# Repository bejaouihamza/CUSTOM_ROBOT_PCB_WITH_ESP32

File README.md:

# CUSTOM_ROBOT_PCB_WITH_ESP32
A custom-designed PCB for robotics applications, featuring the ESP32-C3-WROOM-2 microcontroller with WiFi & Bluetooth connectivity, motor control via the L298P H-bridge, efficient power management, and USB isolation for safe programming.

Key Features
🚀 Core Components
ESP32-C3-WROOM-2 – RISC-V-based MCU with WiFi 4 & Bluetooth 5 (BLE)

L298P Motor Driver – Dual H-bridge for controlling two DC motors or one stepper motor

CH340C USB-UART – Reliable serial communication for programming and debugging

USB Battery Isolation – Prevents backpowering issues during programming

12V Battery Input – Supports LiPo/Li-ion batteries with proper protection

⚡ Power Management
Buck Converter (12V → 5V/3.3V) – Efficient voltage regulation for MCU & peripherals

Battery Monitoring – Optional voltage divider for battery level sensing

🔌 Connectivity & I/O
USB-C Port – For programming & serial communication

Bluetooth/WiFi Control – Remote operation via smartphone or PC

GPIO Breakout – Access to unused ESP32 pins for sensors & expansions

🛠️ Applications
Autonomous Robots (Line-following, obstacle avoidance)

RC Vehicles (WiFi/Bluetooth-controlled)

IoT-Enabled Robotics (Telemetry, remote control)

📌 Schematic & Design Files
Designed in KiCad (schematics & PCB layout included)

Gerber files ready for manufacturing

🔧 Getting Started
Flash the ESP32-C3 via USB-C .

Power via 12V battery – The buck converter supplies stable 5V/3.3V to the system.

Control motors via the L298P using PWM signals from the ESP32.

Use WiFi/BLE for wireless communication (Arduino/ESP-IDF supported).

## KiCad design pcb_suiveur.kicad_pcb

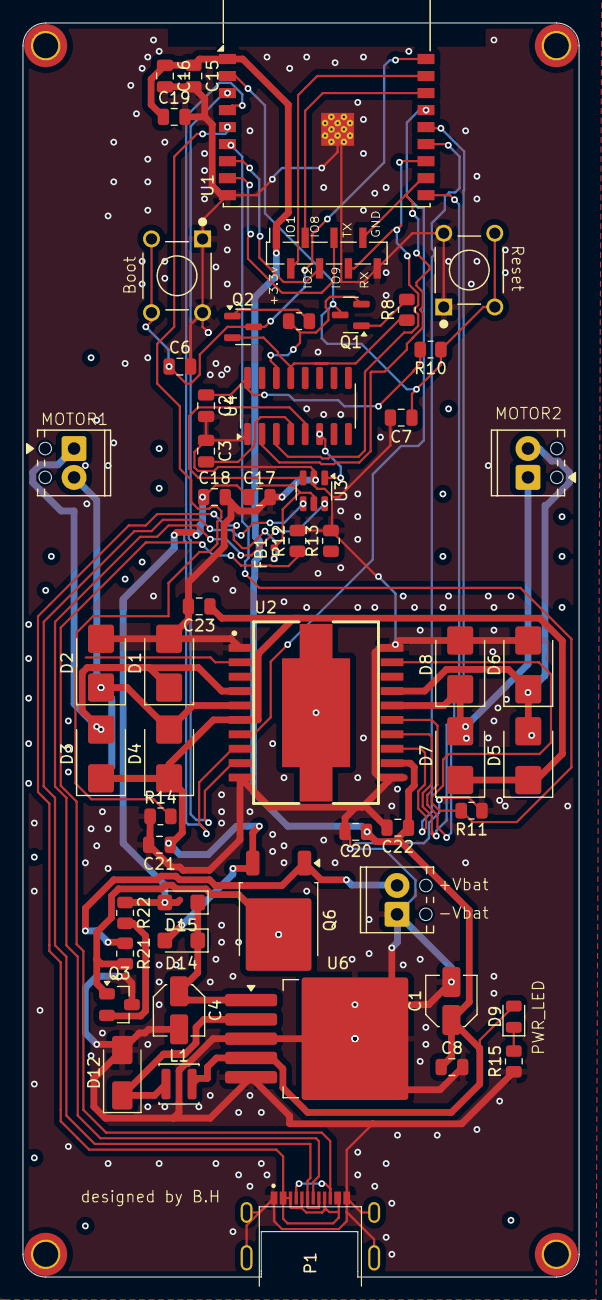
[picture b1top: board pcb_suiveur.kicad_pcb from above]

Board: 2 copper layers, 49.0 x 110.5 mm, 60 parts (0 on the bottom side), 42 nets.

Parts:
C1: 330uf; C_Elec_4x5.4
C2, C3, C6, C8, C15, C20, C21, C22, C23: 0.1u; C_0805_2012Metric
C4: 470u; C_Elec_4x5.4
C7, C17: 1u; C_0805_2012Metric
C16: 22u; C_0805_2012Metric
C18, C19: 10u; C_0805_2012Metric
D1, D2, D3, D4, D5, D6, D7, D8: 1N5819; D_SMB
D9: LED; LED_0805_2012Metric
D12: SS34; D_SMA
D14, D15: 1N5819; D_SMF
FB1: FerriteBead; L_0402_1005Metric
H1, H2, H3, H4: MountingHole; MountingHole_2.2mm_M2_DIN965_Pad_TopOnly
J1: Conn_01x08_Socket; PinSocket_1x08_P1.27mm_Vertical_SMD_Pin1Right
J2, J3, J4_battery3: Screw_Terminal_01x02; TerminalBlock_Phoenix_MPT-0,5-2-2.54_1x02_P2.54mm_Horizontal
L1: 33u; L_APV_ANR3010
P1: USB_C_Plug_USB2.0; TE_2340901-1
Q1, Q2: BC817; SOT-23
Q3: NPN; SuperSOT-3
Q6: NMOS; TO-252-2
R8, R9, R10, R15: 10K; R_0805_2012Metric
R11, R14: 1; R_0805_2012Metric
R12, R13: 5.1K; R_0805_2012Metric
R21: 10k; R_0805_2012Metric
R22: 4.7k; R_0805_2012Metric
SW1, SW2: 1101NE; SW_FSM8JH
U1: ESP32-C3-WROOM-02
U2: L298P; SOIC127P1420X360-20N
U3: USBLC6-2SC6; SOT-23-6
U4: CH340C; SOIC-16_3.9x9.9mm_P1.27mm
U6: LM2596S-3.3; TO-263-5_TabPin3

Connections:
3.3V: C2.1, R10.2, U4.16 (VCC)
+3.3V: C1.1, C8.1, C15.1, C16.1, C19.1, C20.1, C22.1, D9.2 (A), J1.1, L1.2, U1.1 (3V3), U2.12 (Vss), U6.4 (FB)
+Vbat: C21.1, C23.1, D3.1 (K), D4.1 (K), D5.1 (K), D7.1 (K), D14.2 (A), Q6.3 (S), U2.6 (Vs)
/BOOT: C6.1, Q2.3 (C), SW1.2, SW1.4, U1.18 (IO0)
/DTR: Q2.2 (E), R8.1, U4.13 (~DTR)
/EN: C7.1, Q1.3 (C), R10.1, SW2.2, SW2.4, U1.2 (EN)
/ENA: U1.4 (IO5), U2.8 (EnA)
/ENB: U1.10 (IO10), U2.14 (EnB)
/GPIO1: J1.2, U1.17 (IO1)
/GPIO2: J1.3, U1.16 (IO2)
/GPIO8: J1.4, U1.7 (IO8)
/GPIO9: J1.5, U1.8 (IO9)
/IN1: U1.15 (IO3), U2.7 (IN1)
/IN2: U1.3 (IO4), U2.9 (IN2)
/IN3: U1.13 (IO18), U2.13 (IN3)
/IN4: U1.14 (IO19), U2.15 (IN4)
/RTS: Q1.2 (E), R9.1, U4.14 (~RTS)
/RX_TX: J1.6, U1.12 (IO21/TXD), U4.3 (RXD)
/SENSE_A: R14.2, U1.5 (IO6), U2.2 (SENSE_A)
/SENSE_B: R11.2, U1.6 (IO7), U2.19 (SENSE_B)
/TX_RX: J1.7, U1.11 (IO20/RXD), U4.2 (TXD)
GND: C1.2, C2.2, C3.1, C4.2, C6.2, C7.2, C8.2, C15.2, C16.2, C17.2, C18.2, C19.2, C20.2, C21.2, C22.2, C23.2, D1.2 (A), D2.2 (A), D6.2 (A), D8.2 (A), D12.2 (A), J1.8, J4_battery3.1, P1.A1 (GND), Q3.3 (E), R11.1, R12.2, R13.2, R14.1, R15.1, SW1.1, SW1.3, SW2.1, SW2.3, U1.9 (GND), U1.19 (GND), U2.1 (GND), U2.10 (GND), U2.11 (GND), U2.20 (GND), U3.2 (GND), U4.1 (GND), U6.3 (GND), U6.5 (~ON/OFF)
unnamed: D1.1 (K), D3.2 (A), J2.1, U2.4 (OUT1)
unnamed: D2.1 (K), D4.2 (A), J2.2, U2.5 (OUT2)
unnamed: D5.2 (A), D6.1 (K), J3.2, U2.17 (OUT4)
unnamed: D7.2 (A), D8.1 (K), J3.1, U2.16 (OUT3)
unnamed: D9.1 (K), R15.2
unnamed: D12.1 (K), L1.1, U6.2 (OUT)
unnamed: C4.1, D14.1 (K), D15.1 (K), U6.1 (VIN)
unnamed: FB1.1, P1.A9 (VBUS)
unnamed: J4_battery3.2, Q6.1 (D), R21.1
unnamed: P1.A5 (CC), R12.1
unnamed: P1.A6 (D+), U3.4 (I/O2)
unnamed: P1.A7 (D-), U3.6 (I/O1)
unnamed: Q1.1 (B), R8.2
unnamed: Q2.1 (B), R9.2
unnamed: Q3.2 (B), R22.2
unnamed: Q3.1 (C), Q6.2 (G), R21.2
unnamed: U3.3 (I/O2), U4.5 (UD+)
unnamed: U3.1 (I/O1), U4.6 (UD-)
unnamed: C3.2, U4.4 (V3)
VBUS: C17.1, C18.1, D15.2 (A), FB1.2, R22.1, U3.5 (VBUS)
